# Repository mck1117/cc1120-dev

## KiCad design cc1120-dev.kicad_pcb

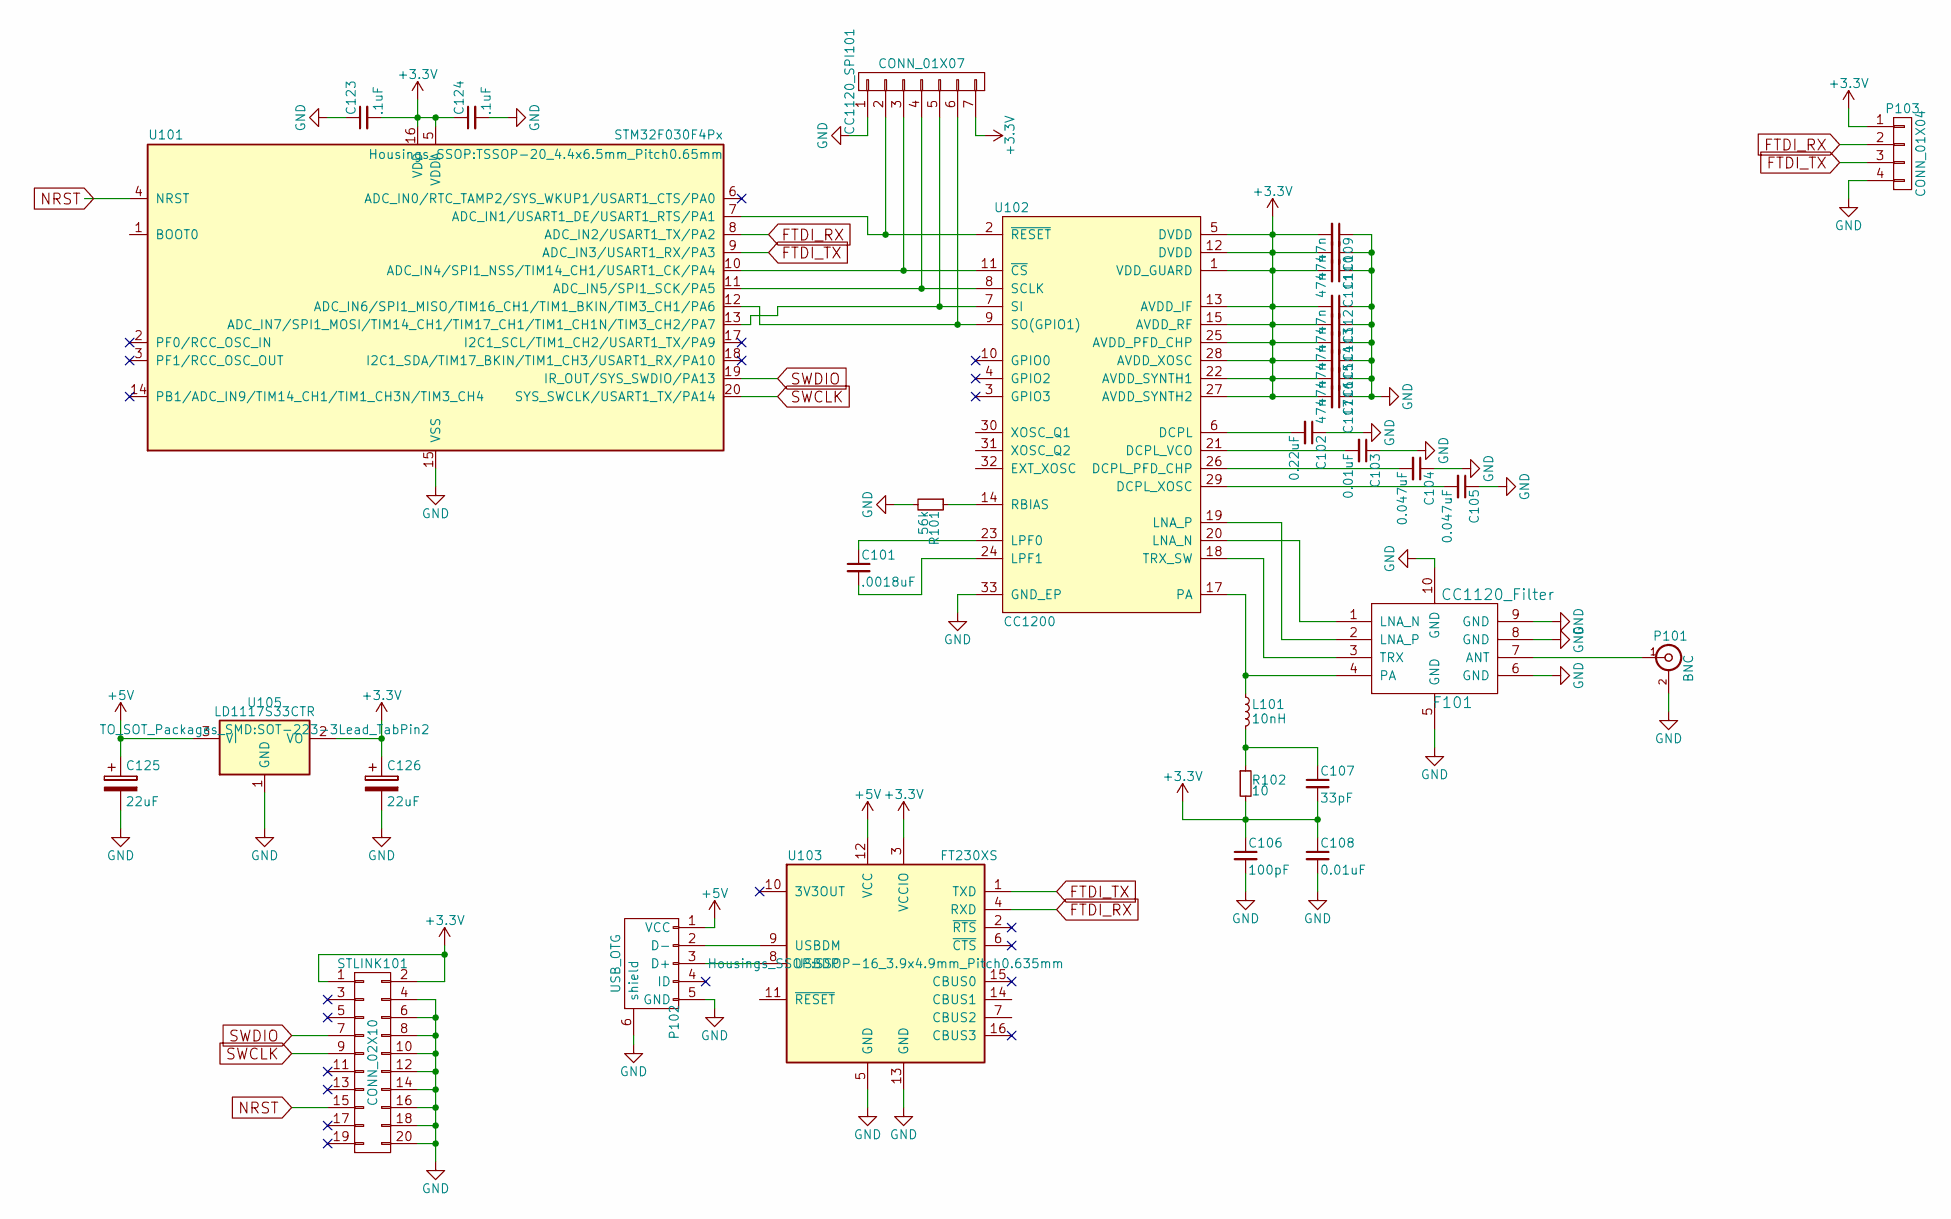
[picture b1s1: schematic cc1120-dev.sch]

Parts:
C101: .0018uF; C_0402
C102: 0.22uF; C_0402
C103: 0.01uF; C_0402
C104, C105: 0.047uF; C_0402
C106: 100pF; C_0402_NoSilk
C107: 33pF; C_0402_NoSilk
C108: 0.01uF; C_0402_NoSilk
C109, C110, C111, C112, C113, C114, C115, C116, C117: 47n; C_0402
C123, C124: .1uF; C_0402_NoSilk
C125, C126: 22uF; CP_Tantalum_Case-B_EIA-3528-21_Reflow
CC1120_SPI101: CONN_01X07; Pin_Header_Straight_1x07_Pitch2.54mm
F101: CC1120_Filter
L101: 10nH; C_0402_NoSilk
P101: BNC; SMA_THT_Jack_Straight
P102: USB_OTG; USB_Mini-B
P103: CONN_01X04; Pin_Header_Straight_1x04_Pitch2.54mm
R101: 56k; R_0402_NoSilk
R102: 10; R_0402_NoSilk
STLINK101: CONN_02X10; Pin_Header_Straight_2x10_Pitch2.54mm
U101: STM32F030F4Px; TSSOP-20_4.4x6.5mm_Pitch0.65mm
U102: CC1200; QFN-32-1EP_5x5mm_Pitch0.5mm
U103: FT230XS; SSOP-16_3.9x4.9mm_Pitch0.635mm
U105: LD1117S33CTR; SOT-223-3Lead_TabPin2

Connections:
+3V3: C106.1, C107.2, C108.1, C109.2, C110.2, C111.2, C112.2, C113.2, C114.2, C115.2, C116.2, C117.2, C123.2, C124.1, C126.1, CC1120_SPI101.7, P103.1, R102.2, STLINK101.1, STLINK101.2, U101.5 (VDDA), U101.16 (VDD), U102.1 (VDD_GUARD), U102.5 (DVDD), U102.12 (DVDD), U102.13 (AVDD_IF), U102.15 (AVDD_RF), U102.22 (AVDD_SYNTH1), U102.25 (AVDD_PFD_CHP), U102.27 (AVDD_SYNTH2), U102.28 (AVDD_XOSC), U103.3 (VCCIO), U105.2 (VO)
+5V: C125.1, P102.1 (VCC), U103.12 (VCC), U105.3 (VI)
FTDI_RX: P103.2, U101.8 (ADC_IN2/USART1_TX/PA2), U103.4 (RXD)
FTDI_TX: P103.3, U101.9 (ADC_IN3/USART1_RX/PA3), U103.1 (TXD)
GND: C102.1, C103.1, C104.1, C105.1, C106.2, C108.2, C109.1, C110.1, C111.1, C112.1, C113.1, C114.1, C115.1, C116.1, C117.1, C123.1, C124.2, C125.2, C126.2, CC1120_SPI101.1, F101.5 (GND), F101.6 (GND), F101.8 (GND), F101.9 (GND), F101.10 (GND), P101.2 (Ext), P102.5 (GND), P102.6 (shield), P103.4, R101.2, STLINK101.4, STLINK101.6, STLINK101.8, STLINK101.10, STLINK101.12, STLINK101.14, STLINK101.16, STLINK101.18, STLINK101.20, U101.15 (VSS), U102.33 (GND_EP), U103.5 (GND), U103.13 (GND), U105.1 (GND)
NRST: STLINK101.15, U101.4 (NRST)
unnamed: C101.1, U102.23 (LPF0)
unnamed: C101.2, U102.24 (LPF1)
unnamed: C102.2, U102.6 (DCPL)
unnamed: C103.2, U102.21 (DCPL_VCO)
unnamed: C104.2, U102.26 (DCPL_PFD_CHP)
unnamed: C105.2, U102.29 (DCPL_XOSC)
unnamed: C107.1, L101.2, R102.1
unnamed: CC1120_SPI101.2, U101.7 (ADC_IN1/USART1_DE/USART1_RTS/PA1), U102.2 (~RESET~)
unnamed: CC1120_SPI101.3, U101.10 (ADC_IN4/SPI1_NSS/TIM14_CH1/USART1_CK/PA4), U102.11 (~CS~)
unnamed: CC1120_SPI101.4, U101.11 (ADC_IN5/SPI1_SCK/PA5), U102.8 (SCLK)
unnamed: CC1120_SPI101.5, U101.13 (ADC_IN7/SPI1_MOSI/TIM14_CH1/TIM17_CH1/T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), U102.7 (SI)
unnamed: CC1120_SPI101.6, U101.12 (ADC_IN6/SPI1_MISO/TIM16_CH1/TIM1_BKIN/T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), U102.9 (SO(GPIO1))
unnamed: F101.1 (LNA_N), U102.20 (LNA_N)
unnamed: F101.2 (LNA_P), U102.19 (LNA_P)
unnamed: F101.3 (TRX), U102.18 (TRX_SW)
unnamed: F101.4 (PA), L101.1, U102.17 (PA)
unnamed: F101.7 (ANT), P101.1 (In)
unnamed: P102.2 (D-), U103.9 (USBDM)
unnamed: P102.3 (D+), U103.8 (USBDP)
unnamed: R101.1, U102.14 (RBIAS)
SWCLK: STLINK101.9, U101.20 (SYS_SWCLK/USART1_TX/PA14)
SWDIO: STLINK101.7, U101.19 (IR_OUT/SYS_SWDIO/PA13)

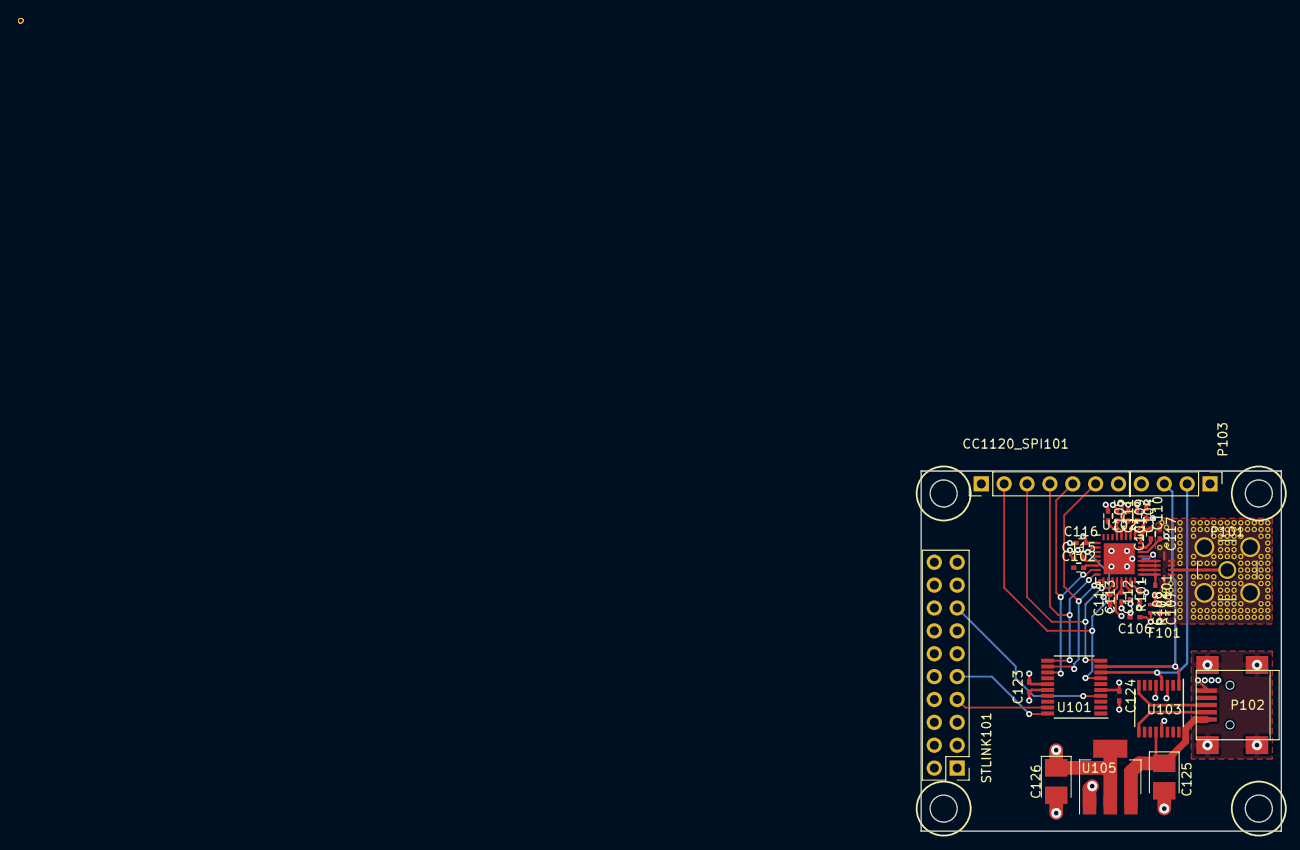
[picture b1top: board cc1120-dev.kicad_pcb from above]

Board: 4 copper layers, 40.0 x 40.0 mm, 34 parts (0 on the bottom side), 28 nets.

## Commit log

2017-03-29 :boom::camel: Added .gitattributes & .gitignore files
2017-03-29 Kicad gitignore
2017-03-29 initial
